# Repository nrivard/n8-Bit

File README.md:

# n8 Bit Microcomputer

The n8 Bit Microcomputer is a homebrew breadboard computer built around a WDC65C02 8-bit CPU.
If you are looking for the software that runs on this computer, check out [LmaOS](https://github.com/nrivard/lmaos).

## History

The n8 Bit was originally a breadboard computer based on the [Ben Eater series of 6502 videos](https://www.youtube.com/playlist?list=PLowKtXNTBypFbtuVMUVXNR0z1mu7dp7eH) but with some added capabilities including ACIA support, GAL-based address decoding logic, and a power chip for more reliable reset and power-on.
Since then, PCBs have been printed and development around the computer is based on these.

## Physical Design

Large PCBs are expensive and I am not a rich person.
For this reason, the main goal of the physical design of this computer and the expansion cards is to fit on the $5 boards at the cheap PCB houses.
This gives a maximum area of 100mm x 100mm, which this board attempts to utilize to the utmost.

## Main Board

The v2 main board is built around a WDC65C02 CPU operating at 3.6864Mhz and is meant to be as minimally viable as possible. It consists of:

* 3 memory sockets (AT28C256/CY62256 footprint) for a configurable mix of RAM and/or ROM
* SC28L92 DUART for serial communication and built-in timer(s)
* CH340 USB-to-serial chip
* Micro USB port for power (D+/D- are connected to the CH340)
* GAL22V10 for flexible address decoding
* Crystal oscillator can for stable clock generation
* 74HC21 for multi-device IRQ and handling (supports older open-collector devices with jumpers on built-in pull-up resistors)
* DS1813 for reset and power-on circuitry
* 3 n8 Bus ports for I/O

### Changes from v1

* Moved from 4 n8 Bus ports down to 3. This was mainly for space reasons and one of the previous ports was always dedicated to serial communication and a VIA for a timer. By moving both of these onto the board, we can give some more breathing room to 3 expansion ports instead
* Moved to half-size oscillator can and increased speed to 3.6864 MHz. The DUART runs at this frequency so I made this the main clock as well.
* Moved to PLCC-44 packaging for CPU and DUART. This not only looks cooler but it has a smaller footprint and allowed me more room to lay out additional components.
* Added transistor stage to the "running" light so it shows when it's actually running, not just when there is power to the board. Pressing and holding RESET will drive this LED off while RESET is low.
* Added qualified (ANDed with CLK) read and write signals to the board and to the n8 Bus ports, replacing D+/D-.
* Ran CLK into the GAL in case I want to use its signal to qualify future signals.
* Moved from 2 layer to 4 layer board. So many signals! Also, this is auto-routed, I don't care, I'm not a purist in this (one) sense

## Address space

By default, the n8 Bit is intended to have the following memory hardware:

* 1 Atmel AT28C256 in the ROM1 socket
* 2 Cypress CY62256NL in the RAM1 and RAM2 sockets

### Default Memory Layout

If you are using the default hardware and the included GAL code, it has the following memory layout:

| Device | Address Range |
|--------|---------------|
| Zero Page | `$0000...$00FF` |
| Stack | `$0100...$01FF` |
| RAM | `$0200...$BEFF` |
| Port 0 | `$BF00...$BF3F` |
| Port 1 | `$BF40...$BF7F` |
| Port 2 | `$BF80...$BFBF` |
| DUART | `$BFC0...$BFFF` |
| ROM | `$C000...$FFFF` |

This configuration has 16K of ROM, 48k (less one page) of RAM, and 1 page of memory (`$BF00...$BFFF`) dedicated to 3 I/O ports and the DUART, each of which has 64 addressable memory locations.

### Customizing the Address Space

Because address decoding is entirely GAL based, you have a lot of room to customize the address space.
The GAL itself has physical connections to each port and to each memory socket for CS signals. How you utilize these (or even _if_ you utilize them) is entirely up to you.
If you wanted a simpler computer (like the Ben Eater computer) you may opt to leave one memory socket open and only use a single RAM and a single ROM chip.
If you go this route, you will have to update your own GAL code to match your hardware configuration.

## n8 Bus

The biggest advancement with the n8 Bit when it moved from breadboards to custom PCBs is the introduction of the n8 Bus spec.

The spec mandates that the following signals will be available on a standard 2x16 board-to-board female header:

**Bidirectional signals:**

* all 8 bits of the data bus

**Read-only signals:**

* bottom 6 bits of the address bus
* per-port dedicated <SPAN STYLE="text-decoration:overline">CS</SPAN> signal
* CPU's R/<SPAN STYLE="text-decoration:overline">W</SPAN> signal
* <SPAN STYLE="text-decoration:overline">READ</SPAN> signal qualified with high part of the CLK
* <SPAN STYLE="text-decoration:overline">WRITE</SPAN> signal qualified with high part of the CLK
* CLK
* <SPAN STYLE="text-decoration:overline">RESET</SPAN>

**Write-only signals:**

* per-port <SPAN STYLE="text-decoration:overline">NMI</SPAN>
* per-port <SPAN STYLE="text-decoration:overline">IRQ</SPAN>

**Expansion signals:**

The n8 Bus spec includes 2 lines (`FUTURE0` and `FUTURE1`) that don't currently have a purpose.
These are hooked up to 2 I/O pins of the GAL and are intended for you to customize them.
For example, if you have a VDP that outputs a colorburst clock that you want to use to drive a sound adapter, you can route that signal through one of these pins.

**Power Rails:**

The n8 Bus spec provides power rails (+5V and ground) on both the top and bottom of the header for shorter, more convenient power routing on your expansions cards.

## I/O Expansion Cards

The main board for this computer is intentionally minimal.
This means that all of your I/O functionality beyond a DUART (VIA, display, sound, etc.) has to come in the form of an expansion card that sits in a n8 Bus port.

### Reference Cards

Two highly utilized devices that many hobbyists want to include on a homebrew computer are a UART (this is unnecessary now on the v2 board but is kept for reference purposes) and a GPIO device.
In this repo, 2 such reference designs are included:

* a UART card based on the Rockwell 65C51, called Kids Serial
* a GPIO (and other functions) card based on the WDC65C22S, called Viaduct

### Custom Cards

If you want to create your own cards, it's best to copy one of the existing reference designs first.
This is because they will already have:

* the n8 Bus port with proper pin directionality _for the card_ in the schematic
* a standardized PCB footprint
* some device footprints (like the 2x16 right-angle male pin header) set

This will ensure you have consistent and correct card designs from the start.

## Interrupts

<SPAN STYLE="text-decoration:overline">NMI</SPAN> and <SPAN STYLE="text-decoration:overline">IRQ</SPAN> are supported for all 3 n8 Bus ports.
This board uses a WDC65C02 which uses a totem-pole design (the NMOS 6502 used an open-drain design) and so the board also includes optional jumpers for pull-up resistors. In general:

* if your device is open-drain (older 6551s) or your device does not support interrupts at all, you will need to **_add_** jumpers across the interrupt lines for that port
* if your device is totem-pole (WDC65C22S), you will want to **_remove_** the jumpers as the pull-up resistor will slow down signal change

See [this article from Garth Wilson](http://wilsonminesco.com/6502primer/IRQconx.html) for more information.

## Known Bugs

There are no known hardware bugs with the v2 board.
If you find one (or more) please raise an issue.

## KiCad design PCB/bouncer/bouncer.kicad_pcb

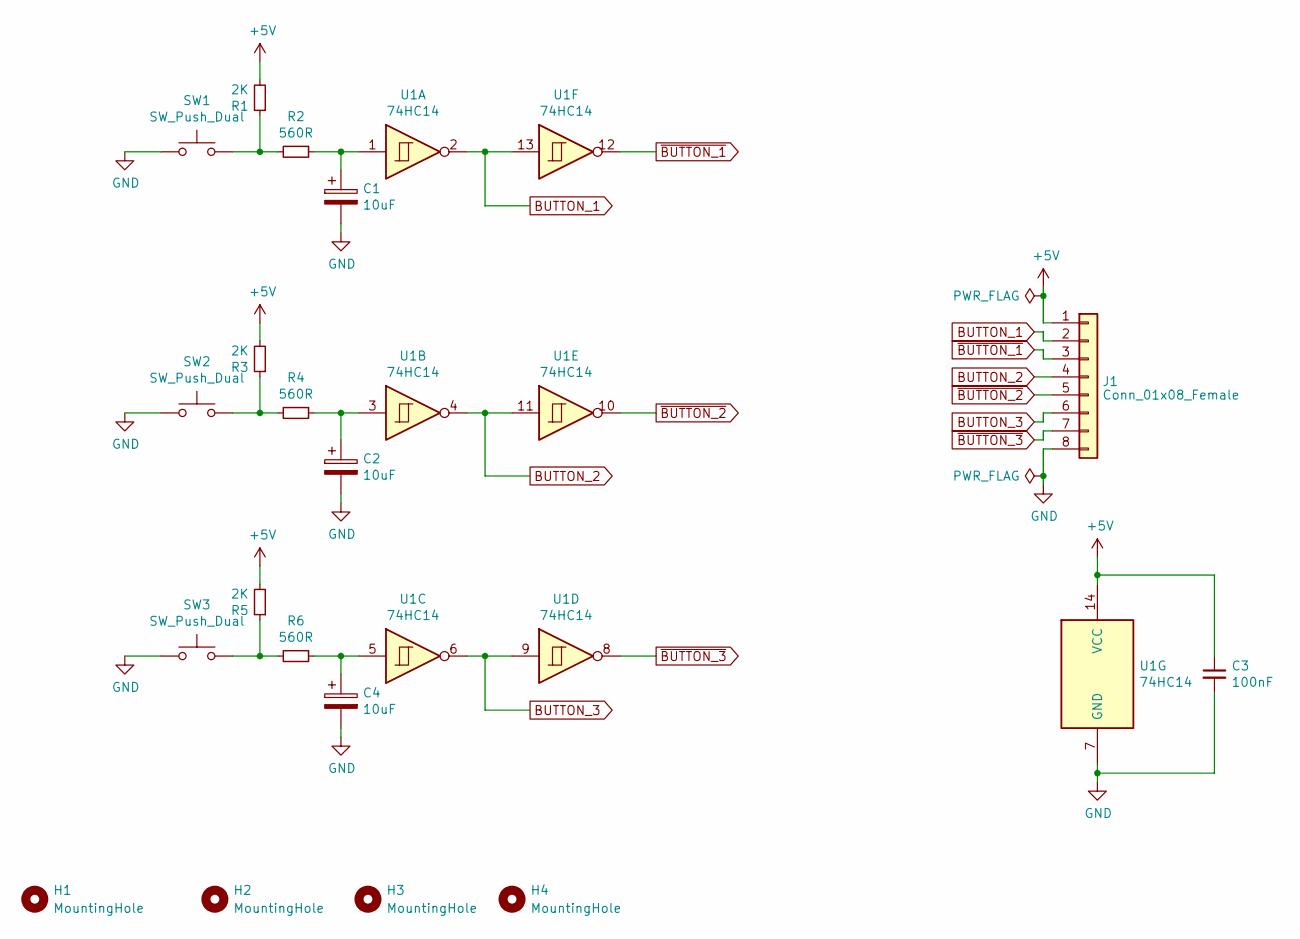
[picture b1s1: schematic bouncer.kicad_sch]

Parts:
C1, C2, C4: 10uF; CP_Radial_D4.0mm_P2.00mm
C3: 100nF; C_Disc_D5.0mm_W2.5mm_P2.50mm
H1, H2, H3, H4: MountingHole; MountingHole_3.2mm_M3_DIN965_Pad
J1: Conn_01x08_Female; PinSocket_1x08_P2.54mm_Vertical
R1, R3, R5: 2K; R_Axial_DIN0207_L6.3mm_D2.5mm_P7.62mm_Horizontal
R2, R4, R6: 560R; R_Axial_DIN0207_L6.3mm_D2.5mm_P7.62mm_Horizontal
SW1, SW2, SW3: SW_Push_Dual; SW_PUSH-12mm
U1: 74HC14; DIP-14_W7.62mm

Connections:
+5V: C3.1, J1.1, R1.2, R3.2, R5.2, U1.14 (VCC)
BUTTON_1: J1.2, U1.2, U1.13
BUTTON_2: J1.4, U1.4, U1.11
BUTTON_3: J1.6, U1.6, U1.9
GND: C1.2, C2.2, C3.2, C4.2, J1.8, SW1.1, SW2.1, SW3.1, U1.7 (GND)
unnamed: C1.1, R2.1, U1.1
unnamed: C2.1, R4.1, U1.3
unnamed: C4.1, R6.1, U1.5
unnamed: R1.1, R2.2, SW1.2
unnamed: R3.1, R4.2, SW2.2
unnamed: R5.1, R6.2, SW3.2
~BUTTON_1: J1.3, U1.12
~BUTTON_2: J1.5, U1.10
~BUTTON_3: J1.7, U1.8

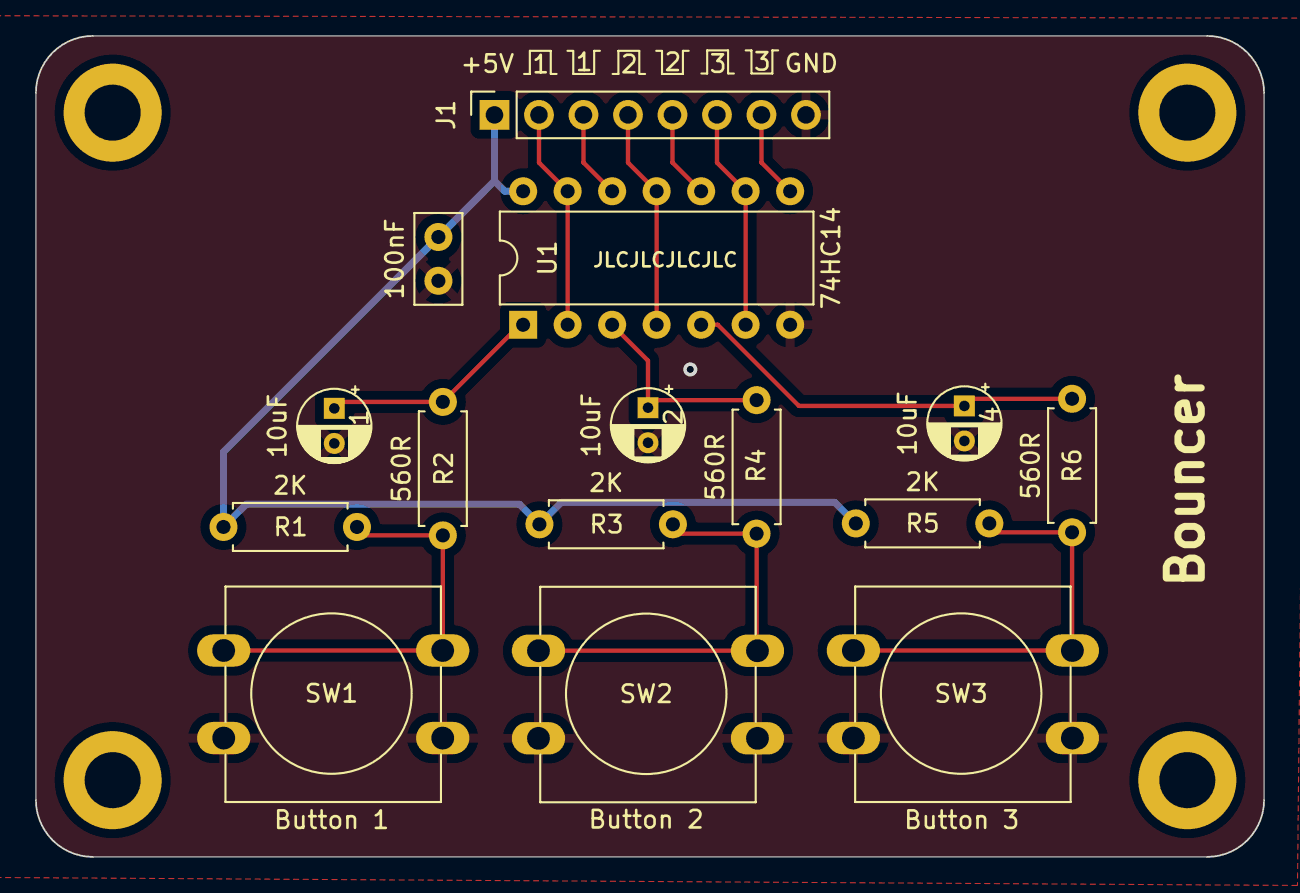
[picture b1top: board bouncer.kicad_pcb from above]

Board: 2 copper layers, 70.1 x 46.9 mm, 19 parts (0 on the bottom side), 14 nets.

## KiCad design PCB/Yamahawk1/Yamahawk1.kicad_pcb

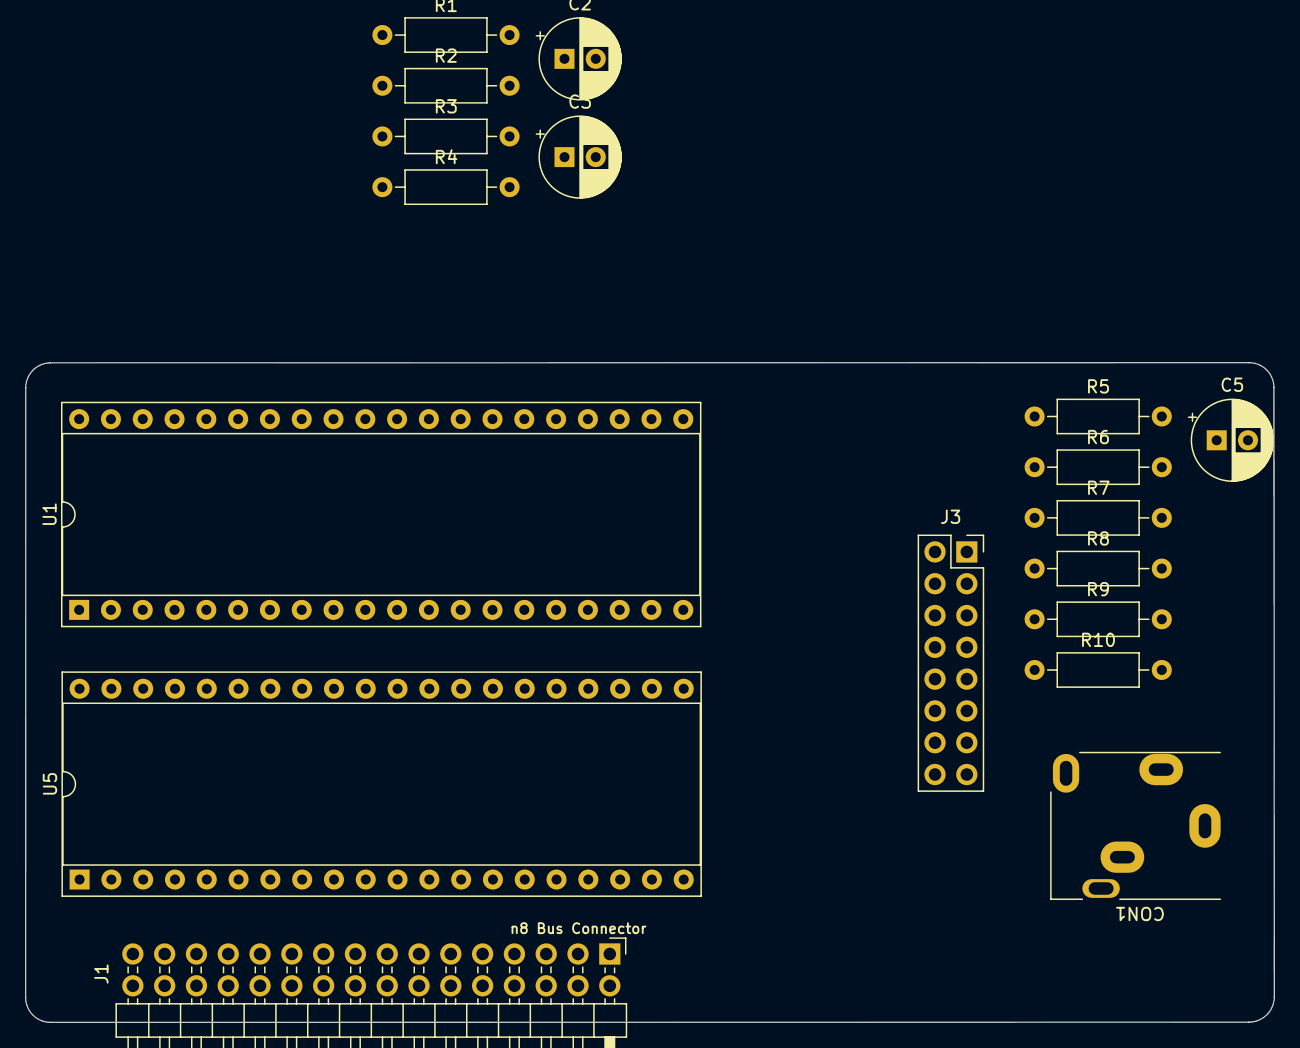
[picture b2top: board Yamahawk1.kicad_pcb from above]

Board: 2 copper layers, 99.7 x 52.7 mm, 18 parts (0 on the bottom side), 39 nets, no tracks yet.

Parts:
C2, C3: 4.7uF; CP_Radial_D6.3mm_P2.50mm
C5: 220uf; CP_Radial_D6.3mm_P2.50mm
CON1: SJ1-3523N; Jack_3.5mm_CUI_SJ1-3515N_Horizontal
J1: n8 Bus Connector; PinHeader_2x16_P2.54mm_Horizontal
J3: SPKR_{OUT}; PinSocket_2x08_P2.54mm_Vertical
R1, R2, R3: 3K; R_Axial_DIN0207_L6.3mm_D2.5mm_P10.16mm_Horizontal
R4, R5: 1K; R_Axial_DIN0207_L6.3mm_D2.5mm_P10.16mm_Horizontal
R6, R7: 1K6; R_Axial_DIN0207_L6.3mm_D2.5mm_P10.16mm_Horizontal
R8, R9: 8K2; R_Axial_DIN0207_L6.3mm_D2.5mm_P10.16mm_Horizontal
R10: 10R; R_Axial_DIN0207_L6.3mm_D2.5mm_P10.16mm_Horizontal
U1: YM2149; DIP-40_W15.24mm_Socket
U5: 65C22S; DIP-40_W15.24mm_Socket

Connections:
+5V: J1.3, J1.4, J1.31, J1.32, U1.25 (A8), U1.28 (BC2), U1.40 (VCC), U5.20 (VDD), U5.24 (CS1)
/A0: J1.28, U5.38 (RS0)
/A1: J1.26, U5.37 (RS1)
/A2: J1.24, U5.36 (RS2)
/A3: J1.22, U5.35 (RS3)
/D0: J1.27, U5.33 (D0)
/D1: J1.25, U5.32 (D1)
/D2: J1.23, U5.31 (D2)
/D3: J1.21, U5.30 (D3)
/D4: J1.19, U5.29 (D4)
/D5: J1.17, U5.28 (D5)
/D6: J1.15, U5.27 (D6)
/D7: J1.13, U5.26 (D7)
/LEFT: C2.2, CON1.T
/PA0: U1.37 (DA0), U5.2 (PA0)
/PA1: U1.36 (DA1), U5.3 (PA1)
/PA2: U1.35 (DA2), U5.4 (PA2)
/PA3: U1.34 (DA3), U5.5 (PA3)
/PA4: U1.33 (DA4), U5.6 (PA4)
/PA5: U1.32 (DA5), U5.7 (PA5)
/PA6: U1.31 (DA6), U5.8 (PA6)
/PA7: U1.30 (DA7), U5.9 (PA7)
/RIGHT: C3.2, CON1.R
AMP_{LEFT}: CON1.TN, R9.1
AMP_{RIGHT}: CON1.RN, R8.1
BC1: U1.29 (BC1), U5.39 (CA2)
CH_A: R2.1, R5.2, U1.4 (CH_A)
CH_B: R3.1, R4.2, U1.3 (CH_B)
CH_C: R1.1, R6.2, R7.2, U1.38 (CH_C)
CLK: J1.12, U5.25 (PHI2)
GND: CON1.S, J1.1, J1.2, J1.29, J1.30, J3.2, R1.2, R2.2, R3.2, R10.2, U1.1 (GND), U1.24 (~A9), U1.26 (~SEL), U5.1 (VSS)
unnamed: C2.1, R4.1, R7.1
unnamed: C3.1, R5.1, R6.1
unnamed: C5.2, J3.1
unnamed: R8.2, R9.2
R~W: J1.14, U5.22 (R~W)
~CS: J1.16, U5.23 (~CS2)
~IRQ: J1.11, U5.21 (~IRQ)
~RES: J1.10, U5.34 (~RES)

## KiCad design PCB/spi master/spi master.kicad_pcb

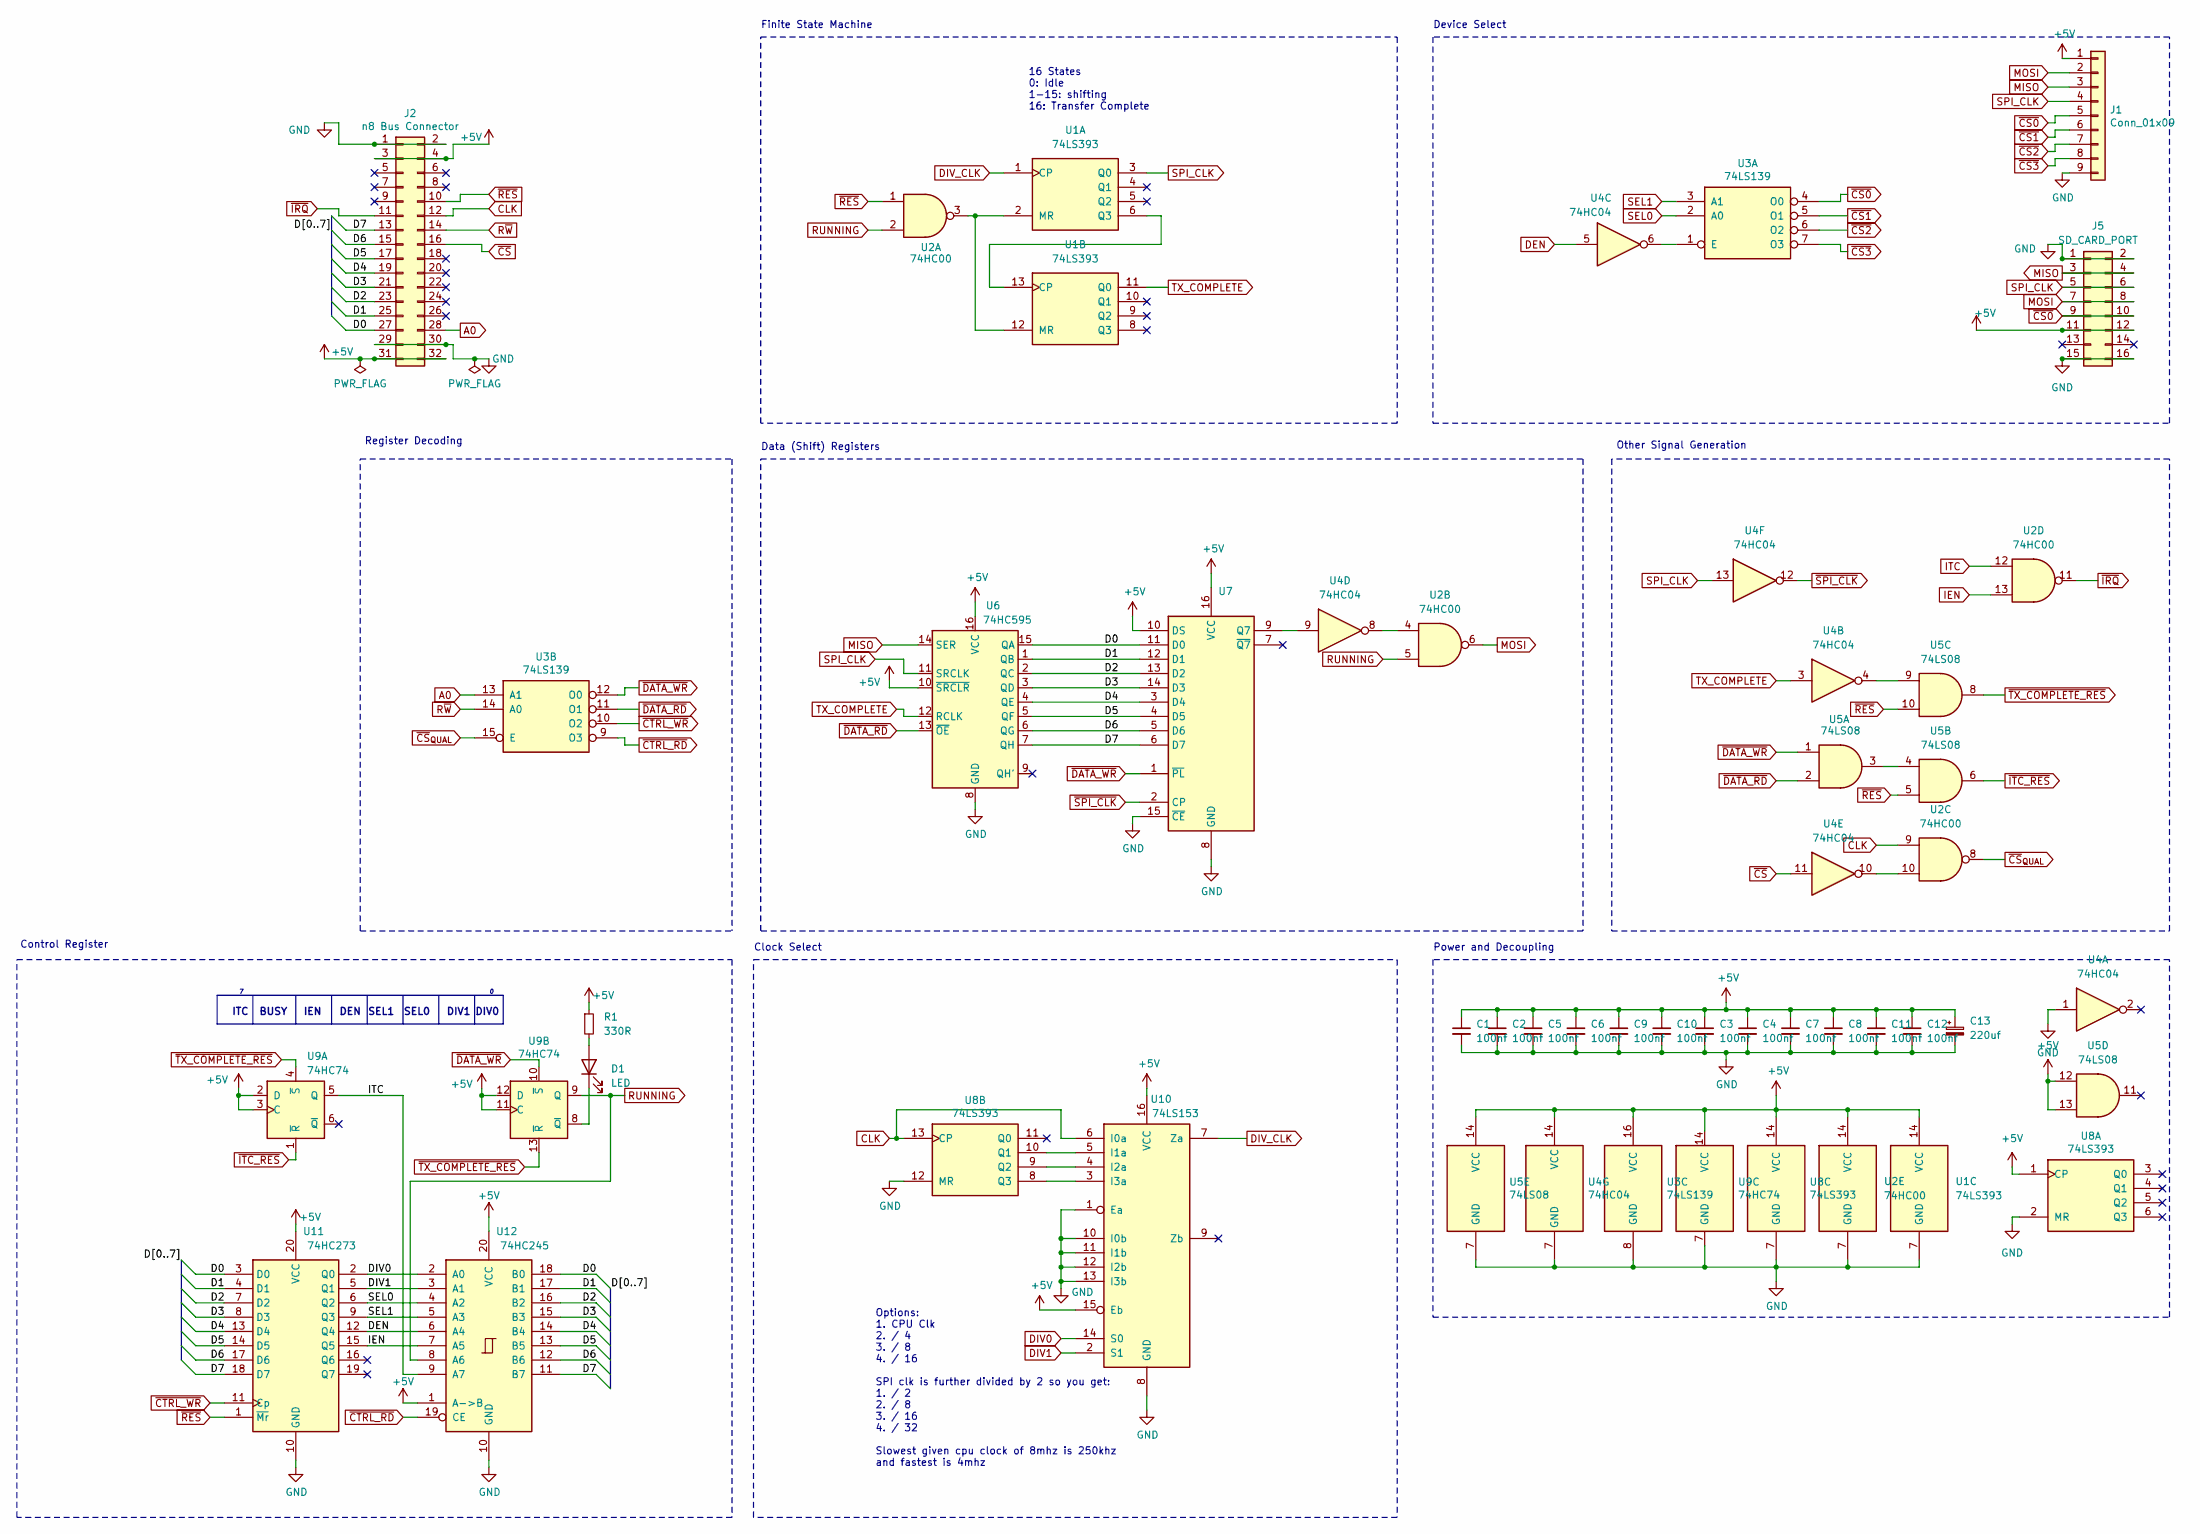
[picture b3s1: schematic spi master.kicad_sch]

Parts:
C1, C2, C3, C4, C5, C6, C7, C8, C9, C10, C11, C12: 100nf; C_Disc_D5.0mm_W2.5mm_P2.50mm
C13: 220uf; CP_Radial_D6.3mm_P2.50mm
D1: LED; LED_0805_2012Metric_Pad1.15x1.40mm_HandSolder
J1: Conn_01x09; PinSocket_1x09_P2.54mm_Horizontal
J2: n8 Bus Connector; PinHeader_2x16_P2.54mm_Horizontal
J5: SD_CARD_PORT; PinSocket_2x08_P2.54mm_Vertical
R1: 330R; R_0805_2012Metric_Pad1.20x1.40mm_HandSolder
U1, U8: 74LS393; DIP-14_W7.62mm_Socket
U2: 74HC00; DIP-14_W7.62mm_Socket
U3: 74LS139; DIP-16_W7.62mm_Socket
U4: 74HC04; DIP-14_W7.62mm_Socket
U5: 74LS08; DIP-14_W7.62mm_Socket
U6: 74HC595; DIP-16_W7.62mm_Socket
U7: 74HC165; DIP-16_W7.62mm_Socket
U9: 74HC74; DIP-14_W7.62mm_Socket
U10: 74LS153; DIP-16_W7.62mm_Socket
U11: 74HC273; DIP-20_W7.62mm_Socket
U12: 74HC245; DIP-20_W7.62mm_Socket

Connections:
+5V: C1.1, C2.1, C3.1, C4.1, C5.1, C6.1, C7.1, C8.1, C9.1, C10.1, C11.1, C12.1, C13.1, J1.1, J2.3, J2.4, J2.31, J2.32, J5.11, J5.12, R1.1, U1.14 (VCC), U2.14 (VCC), U3.16 (VCC), U4.14 (VCC), U5.12, U5.13, U5.14 (VCC), U6.10 (~SRCLR), U6.16 (VCC), U7.10 (DS), U7.16 (VCC), U8.1 (CP), U8.14 (VCC), U9.2 (D), U9.3 (C), U9.11 (C), U9.12 (D), U9.14 (VCC), U10.15 (Eb), U10.16 (VCC), U11.20 (VCC), U12.1 (A->B), U12.20 (VCC)
/D0: J2.27, U6.15 (QA), U7.11 (D0), U11.3 (D0), U12.18 (B0)
/D1: J2.25, U6.1 (QB), U7.12 (D1), U11.4 (D1), U12.17 (B1)
/D2: J2.23, U6.2 (QC), U7.13 (D2), U11.7 (D2), U12.16 (B2)
/D3: J2.21, U6.3 (QD), U7.14 (D3), U11.8 (D3), U12.15 (B3)
/D4: J2.19, U6.4 (QE), U7.3 (D4), U11.13 (D4), U12.14 (B4)
/D5: J2.17, U6.5 (QF), U7.4 (D5), U11.14 (D5), U12.13 (B5)
/D6: J2.15, U6.6 (QG), U7.5 (D6), U11.17 (D6), U12.12 (B6)
/D7: J2.13, U6.7 (QH), U7.6 (D7), U11.18 (D7), U12.11 (B7)
A0: J2.28, U3.13 (A1)
CLK: J2.12, U2.9, U8.13 (CP), U10.6 (I0a)
DEN: U4.5, U11.12 (Q4), U12.6 (A4)
DIV0: U10.14 (S0), U11.2 (Q0), U12.2 (A0)
DIV1: U10.2 (S1), U11.5 (Q1), U12.3 (A1)
DIV_CLK: U1.1 (CP), U10.7 (Za)
GND: C1.2, C2.2, C3.2, C4.2, C5.2, C6.2, C7.2, C8.2, C9.2, C10.2, C11.2, C12.2, C13.2, J1.9, J2.1, J2.2, J2.29, J2.30, J5.1, J5.2, J5.15, J5.16, U1.7 (GND), U2.7 (GND), U3.8 (GND), U4.1, U4.7 (GND), U5.7 (GND), U6.8 (GND), U7.8 (GND), U7.15 (~CE), U8.2 (MR), U8.7 (GND), U8.12 (MR), U9.7 (GND), U10.1 (Ea), U10.8 (GND), U10.10 (I0b), U10.11 (I1b), U10.12 (I2b), U10.13 (I3b), U11.10 (GND), U12.10 (GND)
IEN: U2.13, U11.15 (Q5), U12.7 (A5)
ITC: U2.12, U9.5 (Q), U12.9 (A7)
MISO: J1.3, J5.3, J5.4, U6.14 (SER)
MOSI: J1.2, J5.7, J5.8, U2.6
unnamed: D1.2 (A), R1.2
unnamed: D1.1 (K), U9.8 (~Q)
unnamed: U1.2 (MR), U1.12 (MR), U2.3
unnamed: U1.6 (Q3), U1.13 (CP)
unnamed: U2.4, U4.8
unnamed: U2.10, U4.10
unnamed: U3.1 (E), U4.6
unnamed: U4.4, U5.9
unnamed: U5.3, U5.4
unnamed: U4.9, U7.9 (Q7)
unnamed: U8.10 (Q1), U10.5 (I1a)
unnamed: U8.9 (Q2), U10.4 (I2a)
unnamed: U8.8 (Q3), U10.3 (I3a)
RUNNING: U2.2, U2.5, U9.9 (Q), U12.8 (A6)
R~W: J2.14, U3.14 (A0)
SEL0: U3.2 (A0), U11.6 (Q2), U12.4 (A2)
SEL1: U3.3 (A1), U11.9 (Q3), U12.5 (A3)
SPI_CLK: J1.4, J5.5, J5.6, U1.3 (Q0), U4.13, U6.11 (SRCLK)
TX_COMPLETE: U1.11 (Q0), U4.3, U6.12 (RCLK)
~CS0: J1.5, J5.9, J5.10, U3.4 (O0)
~CS1: J1.6, U3.5 (O1)
~CS2: J1.7, U3.6 (O2)
~CS3: J1.8, U3.7 (O3)
~CS: J2.16, U4.11
~CS_{QUAL}: U2.8, U3.15 (E)
~CTRL_RD: U3.9 (O3), U12.19 (CE)
~CTRL_WR: U3.10 (O2), U11.11 (Cp)
~DATA_RD: U3.11 (O1), U5.2, U6.13 (~OE)
~DATA_WR: U3.12 (O0), U5.1, U7.1 (~PL), U9.10 (~S)
~IRQ: J2.11, U2.11
~ITC_RES: U5.6, U9.1 (~R)
~RES: J2.10, U2.1, U5.5, U5.10, U11.1 (~Mr)
~SPI_CLK: U4.12, U7.2 (CP)
~TX_COMPLETE_RES: U5.8, U9.4 (~S), U9.13 (~R)

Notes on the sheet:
Clock Select
ITC
Control Register
DEN
Other Signal Generation
Finite State Machine
IEN
SEL0
Power and Decoupling
DIV1
Device Select
Options: 1. CPU Clk 2. / 4 3. / 8 4. / 16 SPI clk is further divided by 2 so you get: 1. / 2 2. / 8 3. / 16 4. / 32 Slowest given cpu clock of 8mhz is 250khz and fastest is 4mhz
Register Decoding
Data (Shift) Registers
SEL1
16 States 0: Idle 1-15: shifting 16: Transfer Complete
DIV0
BUSY

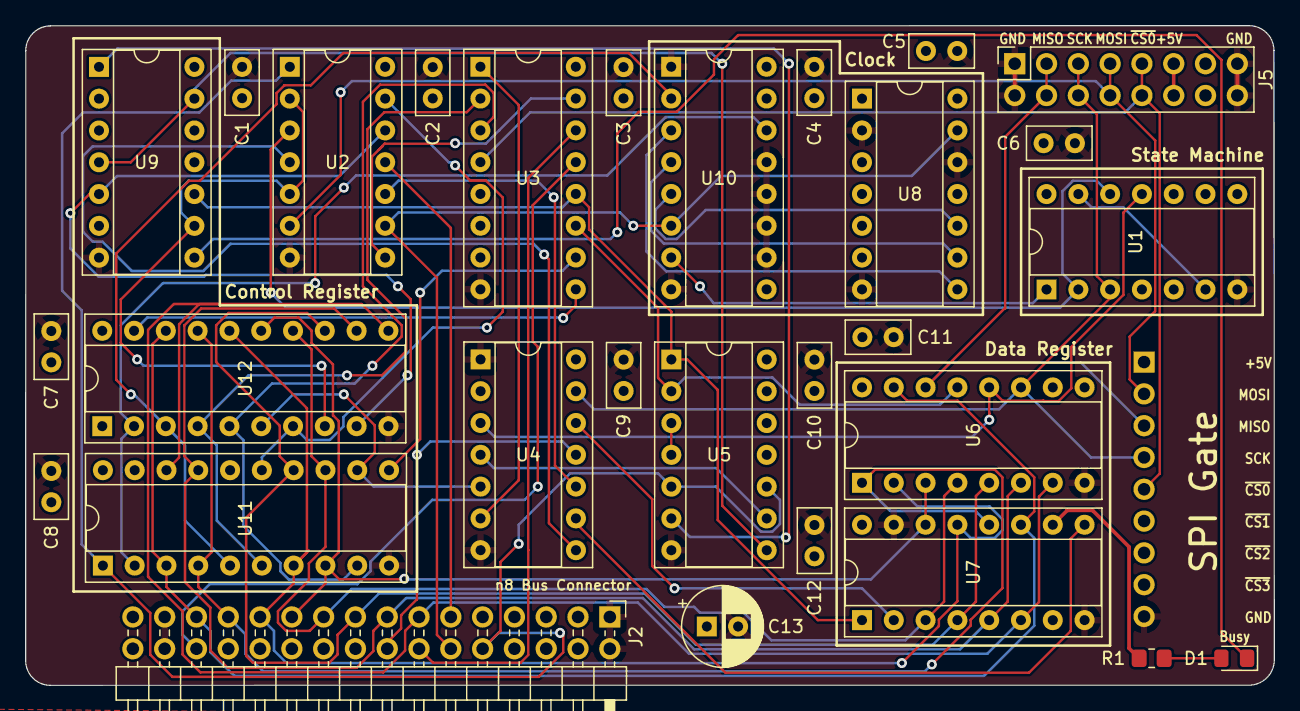
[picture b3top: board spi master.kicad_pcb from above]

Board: 4 copper layers, 99.7 x 52.7 mm, 30 parts (1 on the bottom side), 54 nets.

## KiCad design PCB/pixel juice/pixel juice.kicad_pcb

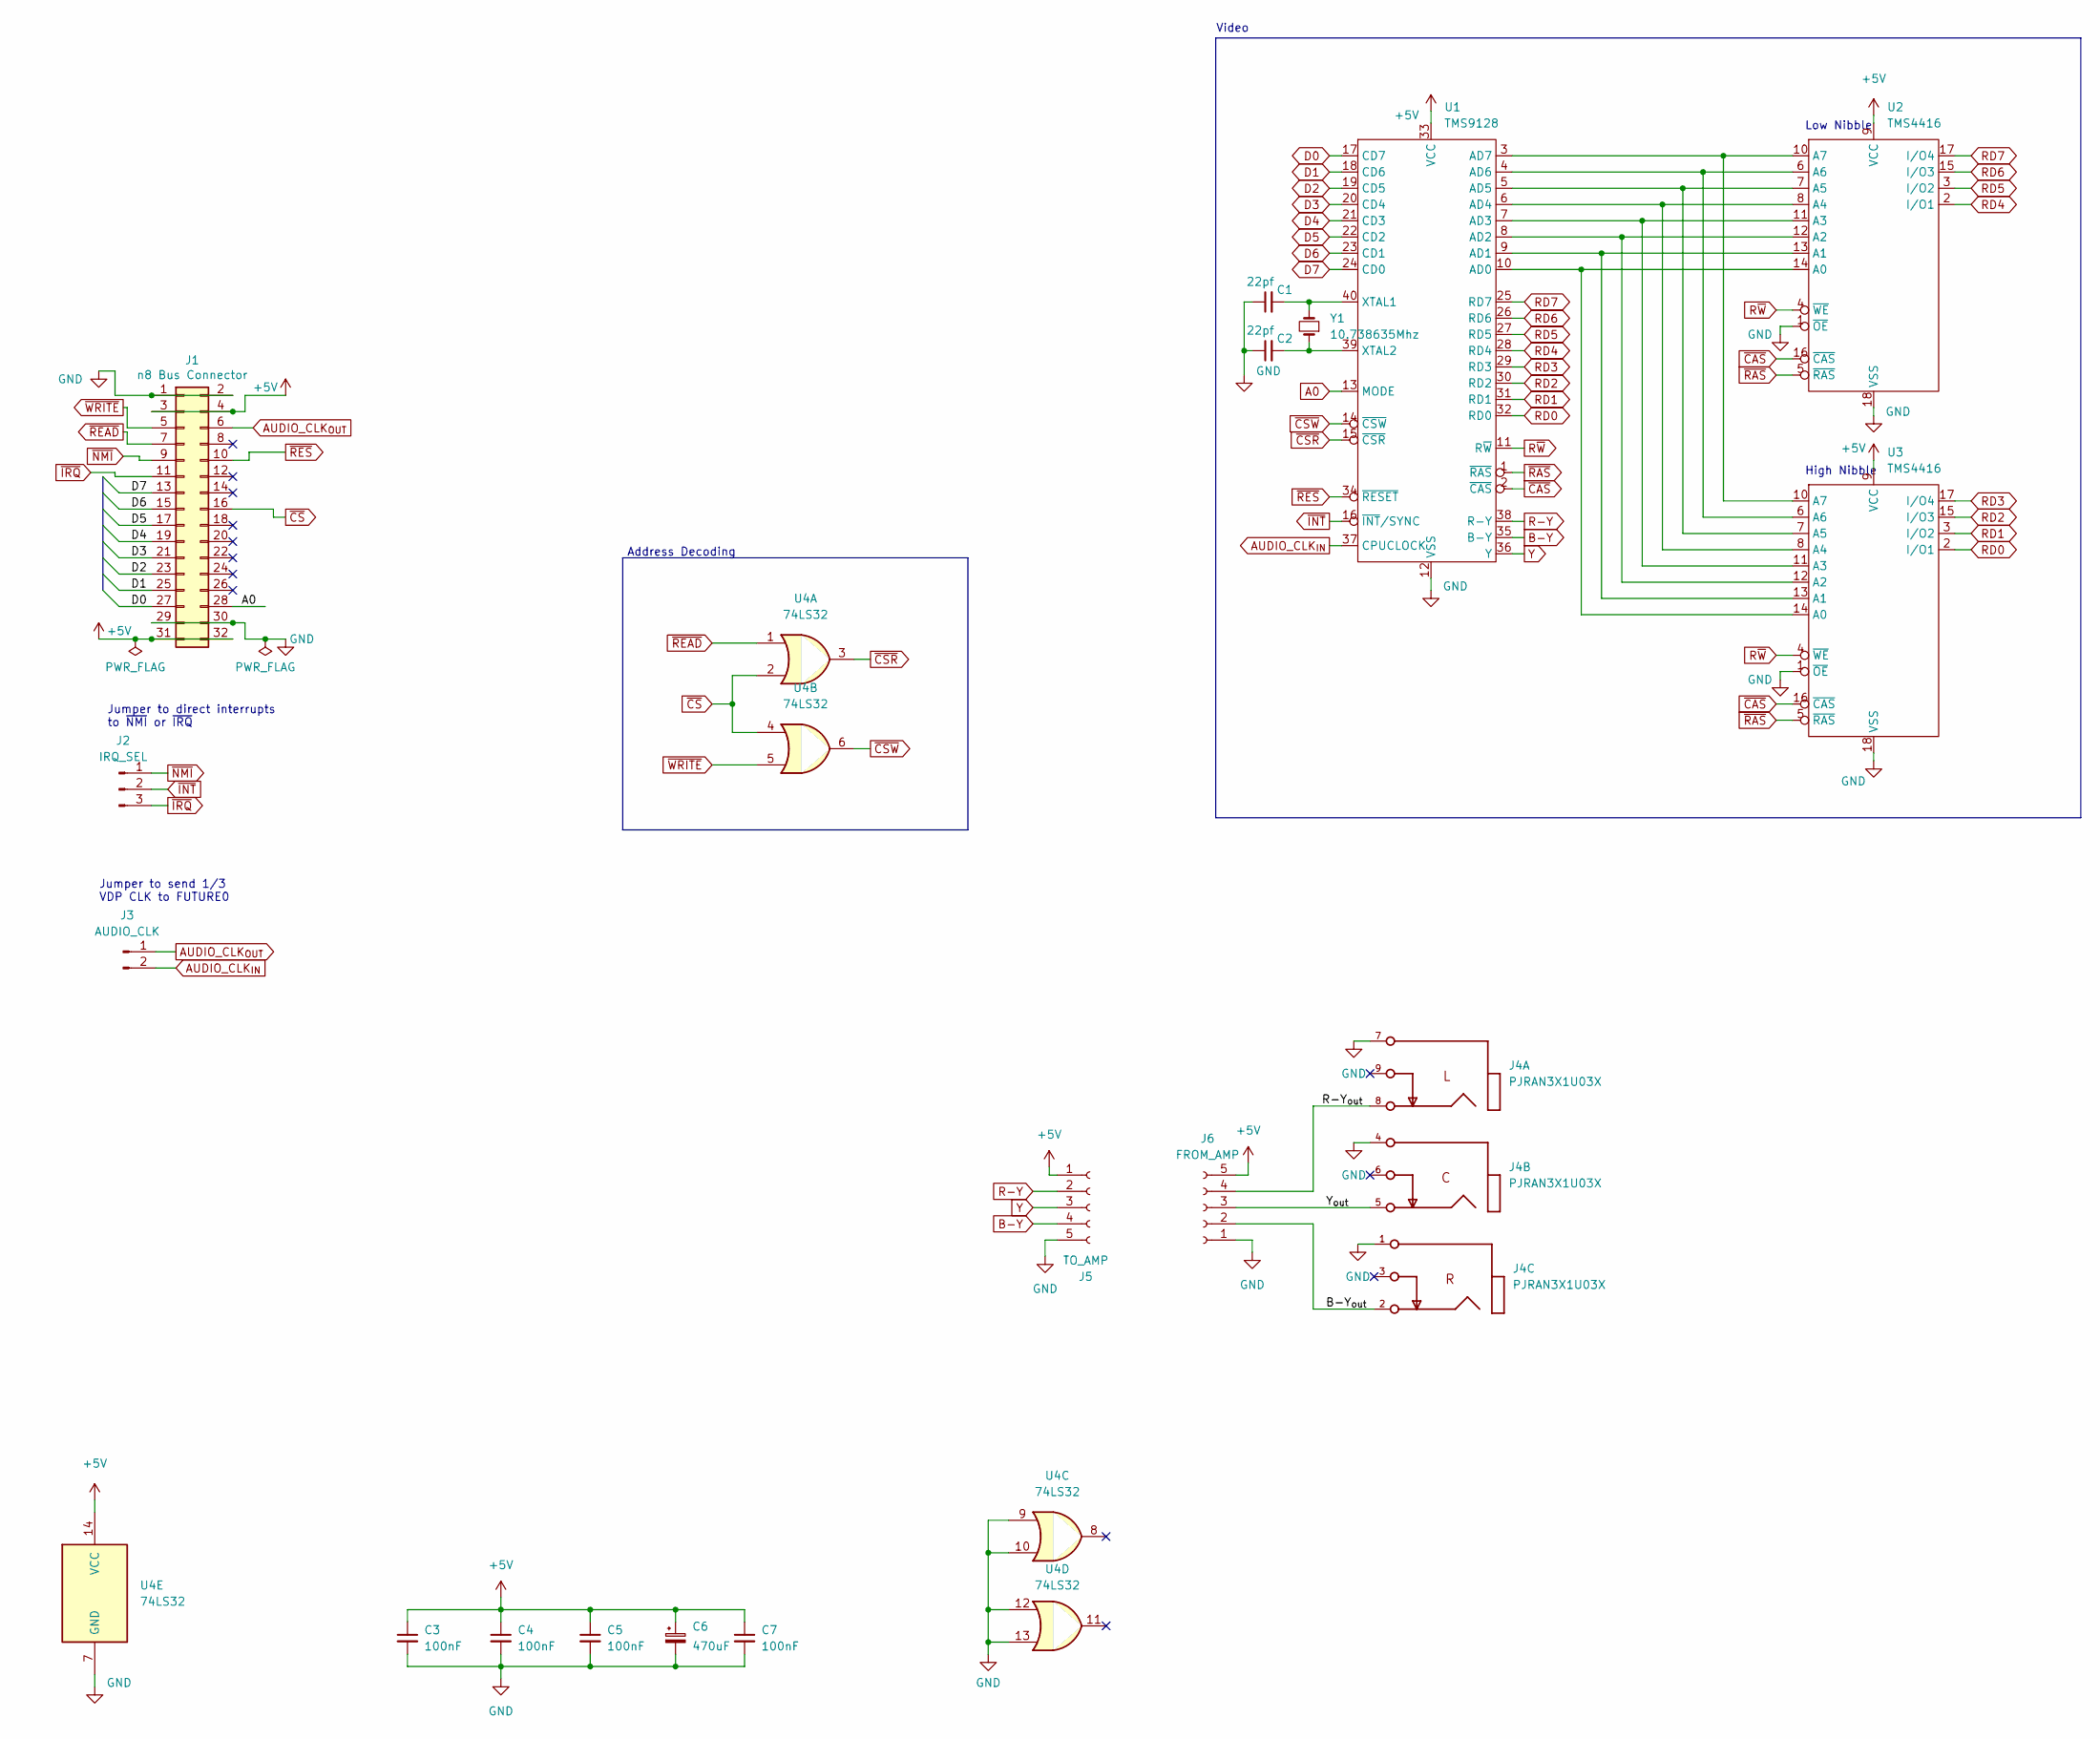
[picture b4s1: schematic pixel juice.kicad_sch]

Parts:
C1, C2: 22pf; C_Disc_D5.0mm_W2.5mm_P2.50mm
C3, C4, C5, C7: 100nF; C_0805_2012Metric_Pad1.18x1.45mm_HandSolder
C6: 470uF; CP_Radial_D8.0mm_P3.80mm
J1: n8 Bus Connector; PinHeader_2x16_P2.54mm_Horizontal
J2: IRQ_SEL; PinHeader_1x03_P2.54mm_Vertical
J3: AUDIO_CLK; PinHeader_1x02_P2.54mm_Vertical
J4: PJRAN3X1U03X; PJRAN3X1U01X
J5: TO_AMP; PinSocket_1x05_P2.54mm_Vertical
J6: FROM_AMP; PinSocket_1x05_P2.54mm_Vertical
U1: TMS9128; DIP-40_W15.24mm_Socket
U2, U3: TMS4416; DIP-18_W7.62mm_Socket
U4: 74LS32; DIP-14_W7.62mm_Socket
Y1: 10.738635Mhz; Crystal_HC49-U_Horizontal

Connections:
+5V: C3.1, C4.1, C5.1, C6.1, C7.1, J1.3, J1.4, J1.31, J1.32, J5.1, J6.5, U1.33 (VCC), U2.9 (VCC), U3.9 (VCC), U4.14 (VCC)
/B-Y_{out}: J4.2, J6.2
/R-Y_{out}: J4.8, J6.4
/Y_{out}: J4.5, J6.3
A0: J1.28, U1.13 (MODE)
AUDIO_CLK_{IN}: J3.2, U1.37 (CPUCLOCK)
AUDIO_CLK_{OUT}: J1.6, J3.1
B-Y: J5.4, U1.35 (B-Y)
D0: J1.27, U1.17 (CD7)
D1: J1.25, U1.18 (CD6)
D2: J1.23, U1.19 (CD5)
D3: J1.21, U1.20 (CD4)
D4: J1.19, U1.21 (CD3)
D5: J1.17, U1.22 (CD2)
D6: J1.15, U1.23 (CD1)
D7: J1.13, U1.24 (CD0)
GND: C1.1, C2.1, C3.2, C4.2, C5.2, C6.2, C7.2, J1.1, J1.2, J1.29, J1.30, J4.1, J4.4, J4.7, J5.5, J6.1, U1.12 (VSS), U2.1 (~OE), U2.18 (VSS), U3.1 (~OE), U3.18 (VSS), U4.7 (GND), U4.9, U4.10, U4.12, U4.13
unnamed: C1.2, U1.40 (XTAL1), Y1.2
unnamed: C2.2, U1.39 (XTAL2), Y1.1
unnamed: U1.3 (AD7), U2.10 (A7), U3.10 (A7)
unnamed: U1.4 (AD6), U2.6 (A6), U3.6 (A6)
unnamed: U1.5 (AD5), U2.7 (A5), U3.7 (A5)
unnamed: U1.6 (AD4), U2.8 (A4), U3.8 (A4)
unnamed: U1.7 (AD3), U2.11 (A3), U3.11 (A3)
unnamed: U1.8 (AD2), U2.12 (A2), U3.12 (A2)
unnamed: U1.9 (AD1), U2.13 (A1), U3.13 (A1)
unnamed: U1.10 (AD0), U2.14 (A0), U3.14 (A0)
R-Y: J5.2, U1.38 (R-Y)
RD0: U1.32 (RD0), U3.2 (I/O1)
RD1: U1.31 (RD1), U3.3 (I/O2)
RD2: U1.30 (RD2), U3.15 (I/O3)
RD3: U1.29 (RD3), U3.17 (I/O4)
RD4: U1.28 (RD4), U2.2 (I/O1)
RD5: U1.27 (RD5), U2.3 (I/O2)
RD6: U1.26 (RD6), U2.15 (I/O3)
RD7: U1.25 (RD7), U2.17 (I/O4)
R~W: U1.11 (R~W), U2.4 (~WE), U3.4 (~WE)
Y: J5.3, U1.36 (Y)
~CAS: U1.2 (~CAS), U2.16 (~CAS), U3.16 (~CAS)
~CSR: U1.15 (~CSR), U4.3
~CSW: U1.14 (~CSW), U4.6
~CS: J1.16, U4.2, U4.4
~INT: J2.2, U1.16 (~INT/SYNC)
~IRQ: J1.11, J2.3
~NMI: J1.9, J2.1
~RAS: U1.1 (~RAS), U2.5 (~RAS), U3.5 (~RAS)
~READ: J1.7, U4.1
~RES: J1.10, U1.34 (~RESET)
~WRITE: J1.5, U4.5

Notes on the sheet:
High Nibble
Low Nibble
Video
Address Decoding
Jumper to send 1/3 VDP CLK to FUTURE0
Jumper to direct interrupts to ~{NMI} or ~{IRQ}

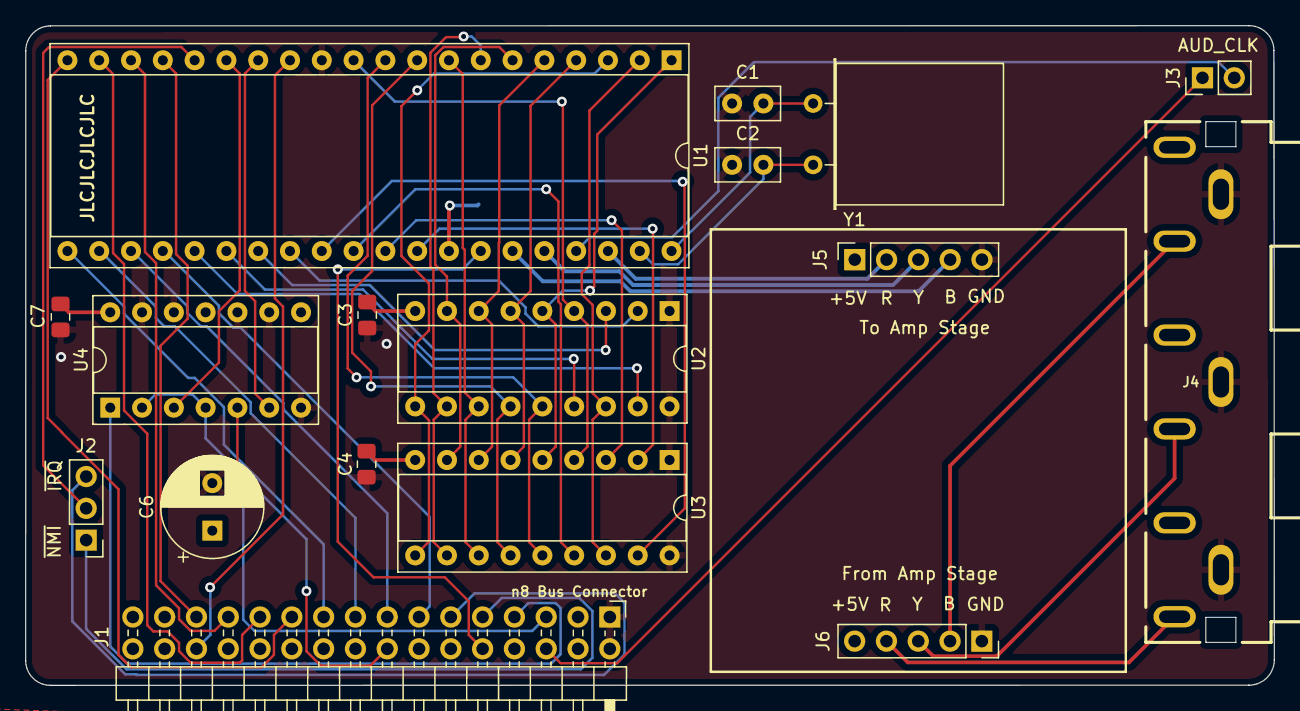
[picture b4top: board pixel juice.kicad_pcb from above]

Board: 4 copper layers, 99.7 x 52.7 mm, 18 parts (1 on the bottom side), 49 nets.

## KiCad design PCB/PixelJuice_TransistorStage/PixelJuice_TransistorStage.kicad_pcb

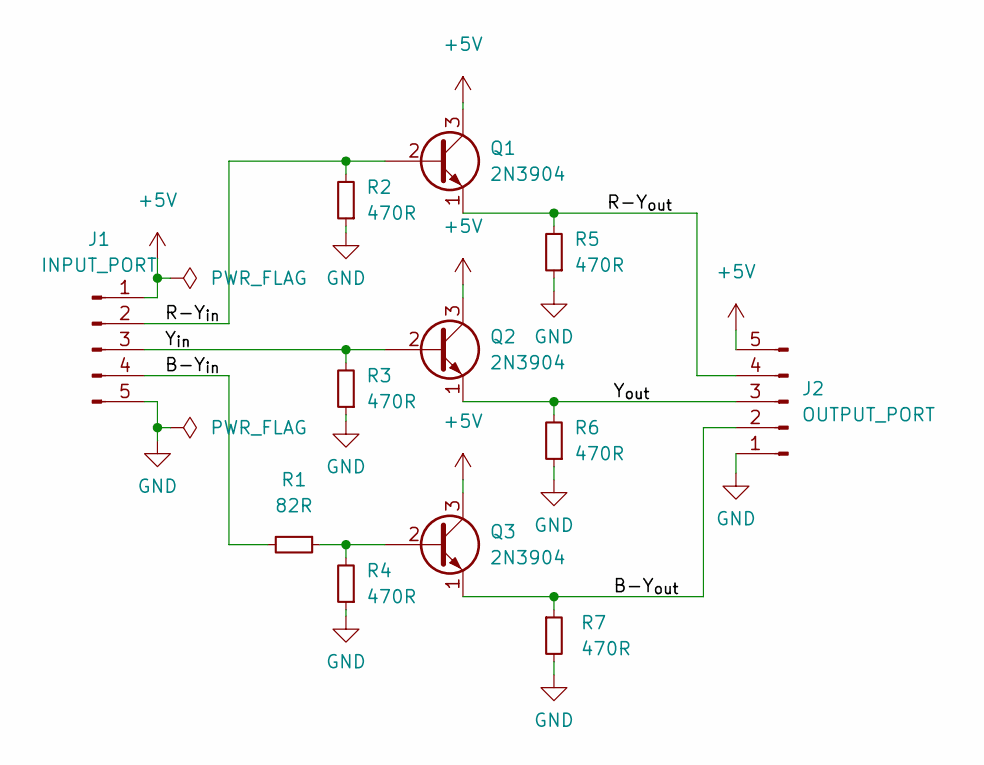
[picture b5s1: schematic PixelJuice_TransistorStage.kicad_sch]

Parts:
J1: INPUT_PORT; PinHeader_1x05_P2.54mm_Vertical
J2: OUTPUT_PORT; PinHeader_1x05_P2.54mm_Vertical
Q1, Q2, Q3: 2N3904; TO-92_Inline
R1: 82R; R_Axial_DIN0207_L6.3mm_D2.5mm_P7.62mm_Horizontal
R2, R3, R4, R5, R6, R7: 470R; R_Axial_DIN0207_L6.3mm_D2.5mm_P7.62mm_Horizontal

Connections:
+5V: J1.1, J2.5, Q1.3 (C), Q2.3 (C), Q3.3 (C)
/B-Y_{in}: J1.4, R1.2
/B-Y_{out}: J2.2, Q3.1 (E), R7.1
/R-Y_{in}: J1.2, Q1.2 (B), R2.2
/R-Y_{out}: J2.4, Q1.1 (E), R5.2
/Y_{in}: J1.3, Q2.2 (B), R3.2
/Y_{out}: J2.3, Q2.1 (E), R6.2
GND: J1.5, J2.1, R2.1, R3.1, R4.1, R5.1, R6.1, R7.2
unnamed: Q3.2 (B), R1.1, R4.2
